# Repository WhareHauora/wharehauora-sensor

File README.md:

# whareora-sensor

# Dependencies

Tested on arduino 1.6.12

## Installing arduino

```
wget http://downloads.arduino.cc/arduino-1.6.12-linux64.tar.xz
tar xf arduino-1.6.12-linux64.tar.xz
sudo mv arduino-1.6.12 /usr/local/share/arduino
sudo ln -s /usr/local/share/arduino/arduino /usr/local/bin/arduino
```

## Programming a sensor

We are working with a fork of the
[sensebender|https://www.openhardware.io/view/1/Sensebender-Micro]
micro circuit. A (only slightly modified) copy of their
example arduino sketch is in `sense_bender` folder. Boards
purchased from sensebender (and assembled) then programmed
with this sketch will talk happily to the Whare Hauora cloud.

See also:
[Sensor Bender Board gitub](https://github.com/mysensors/SensebenderMicro)

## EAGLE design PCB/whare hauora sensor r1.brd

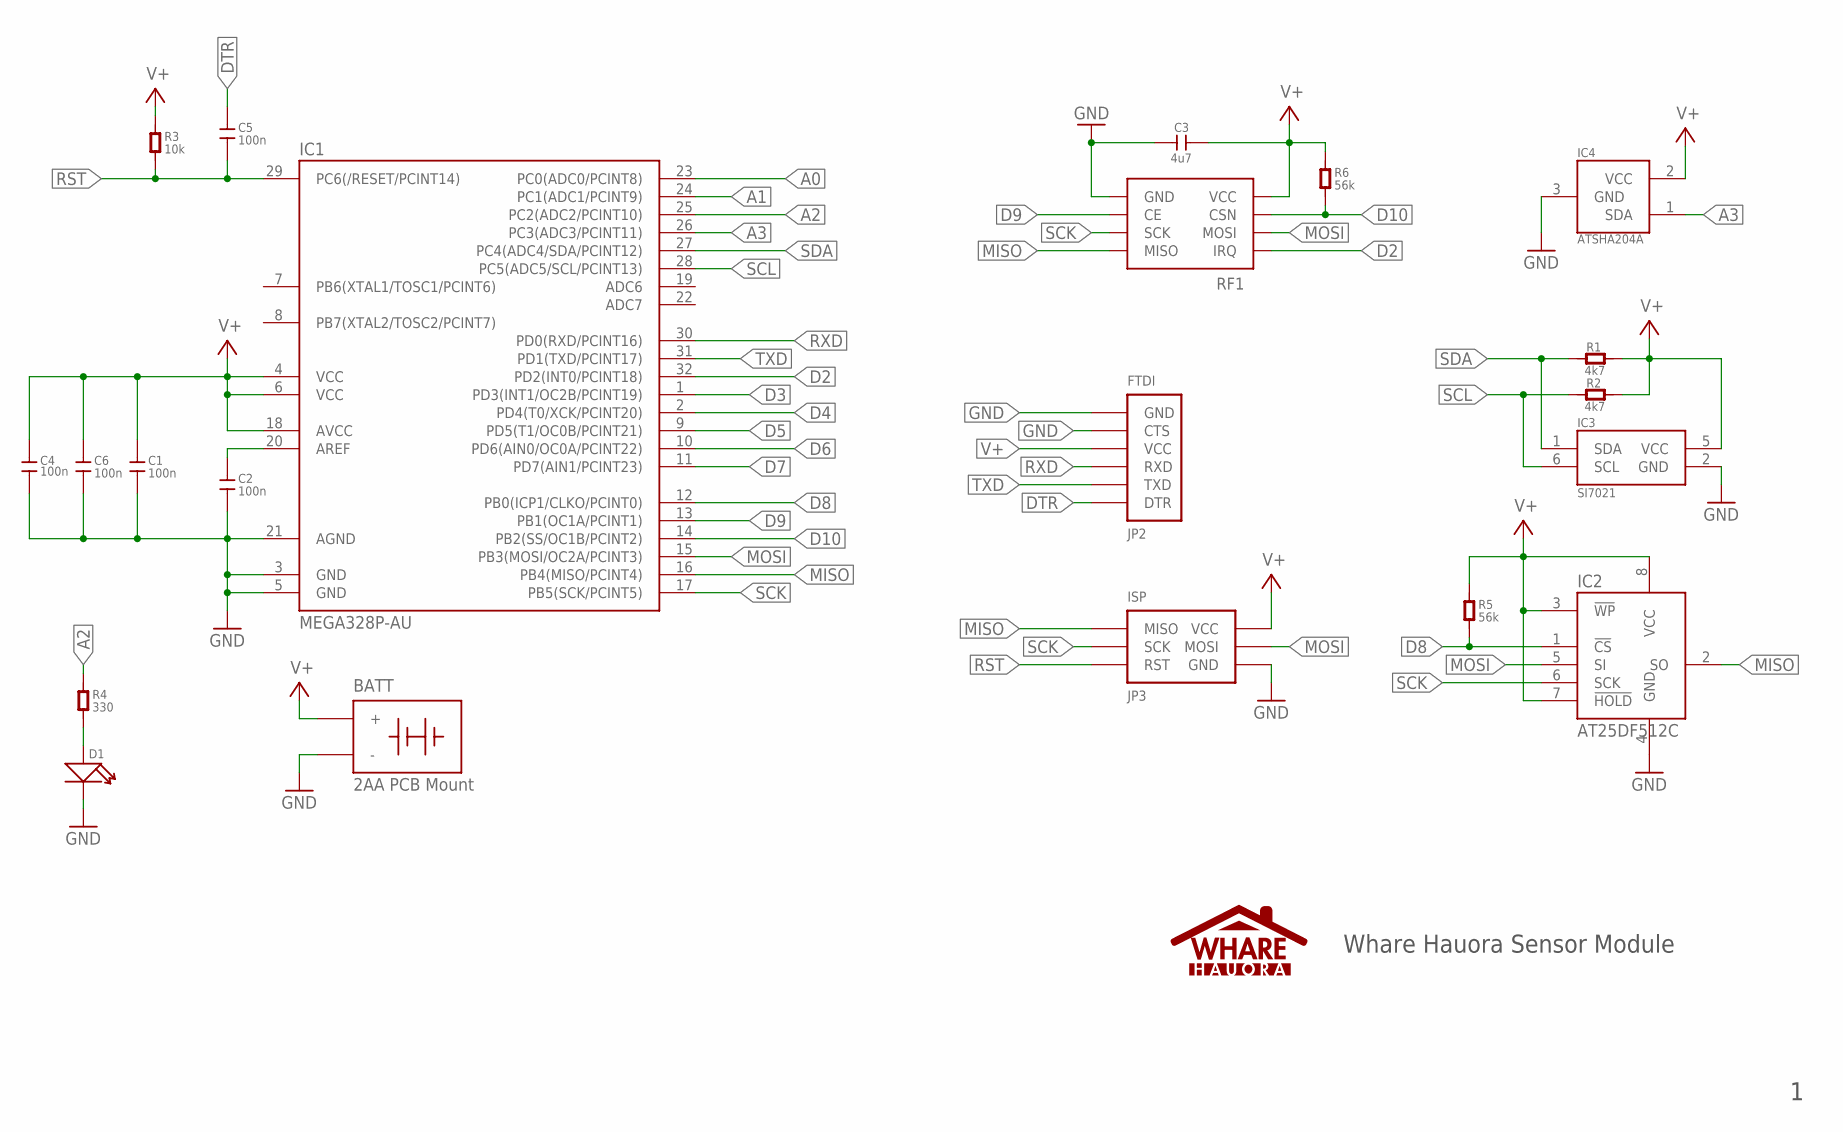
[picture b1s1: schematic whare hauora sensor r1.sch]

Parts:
BATT: 2AA-PACK; 2AA-PACK\
C1, C2, C4, C5, C6: 100n; C0603
C3: 4u7; C0603
D1: LED-0603
IC1: MEGA328P-AU; TQFP32-08
IC2: AT25DF512C; SO8
IC3: SI7021; DFN6
IC4: ATSHA204A; SOT23
JP2: FTDI
JP3: ISP
R1, R2: 4k7; R0603
R3: 10k; R0603
R4: 330; R0603
R5, R6: 56k; R0603
RF1: NRF24L01+

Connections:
A0: IC1.23 (PC0(ADC0/PCINT8))
A1: IC1.24 (PC1(ADC1/PCINT9))
A2: IC1.25 (PC2(ADC2/PCINT10)), R4.1
A3: IC1.26 (PC3(ADC3/PCINT11)), IC4.1 (SDA)
D2: IC1.32 (PD2(INT0/PCINT18)), RF1.P$8 (IRQ)
D3: IC1.1 (PD3(INT1/OC2B/PCINT19))
D4: IC1.2 (PD4(T0/XCK/PCINT20))
D5: IC1.9 (PD5(T1/OC0B/PCINT21))
D6: IC1.10 (PD6(AIN0/OC0A/PCINT22))
D7: IC1.11 (PD7(AIN1/PCINT23))
D8: IC1.12 (PB0(ICP1/CLKO/PCINT0)), IC2.1 (!CS), R5.1
D9: IC1.13 (PB1(OC1A/PCINT1)), RF1.P$3 (CE)
D10: IC1.14 (PB2(SS/OC1B/PCINT2)), R6.1, RF1.P$4 (CSN)
DTR: C5.1, JP2.DTR
GND: BATT.-, C1.2, C2.2, C3.1, C4.2, C6.2, D1.-, IC1.3 (GND), IC1.5 (GND), IC1.21 (AGND), IC2.4 (GND), IC3.2 (GND), IC4.3 (GND), JP2.CTS, JP2.GND, JP3.GND, RF1.P$1 (GND)
MISO: IC1.16 (PB4(MISO/PCINT4)), IC2.2 (SO), JP3.MISO, RF1.P$7 (MISO)
MOSI: IC1.15 (PB3(MOSI/OC2A/PCINT3)), IC2.5 (SI), JP3.MOSI, RF1.P$6 (MOSI)
unnamed: D1.+, R4.2
unnamed: C2.1, IC1.20 (AREF)
RST: C5.2, IC1.29 (PC6(/RESET/PCINT14)), JP3.RST, R3.1
RXD: IC1.30 (PD0(RXD/PCINT16)), JP2.RXD
SCK: IC1.17 (PB5(SCK/PCINT5)), IC2.6 (SCK), JP3.SCK, RF1.P$5 (SCK)
SCL: IC1.28 (PC5(ADC5/SCL/PCINT13)), IC3.6 (SCL), R2.1
SDA: IC1.27 (PC4(ADC4/SDA/PCINT12)), IC3.1 (SDA), R1.1
TXD: IC1.31 (PD1(TXD/PCINT17)), JP2.TXD
V+: BATT.+, C1.1, C3.2, C4.1, C6.1, IC1.4 (VCC), IC1.6 (VCC), IC1.18 (AVCC), IC2.3 (!WP), IC2.7 (!HOLD), IC2.8 (VCC), IC3.5 (VCC), IC4.2 (VCC), JP2.VCC, JP3.VCC, R1.2, R2.2, R3.2, R5.2, R6.2, RF1.P$2 (VCC)

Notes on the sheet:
Whare Hauora Sensor Module

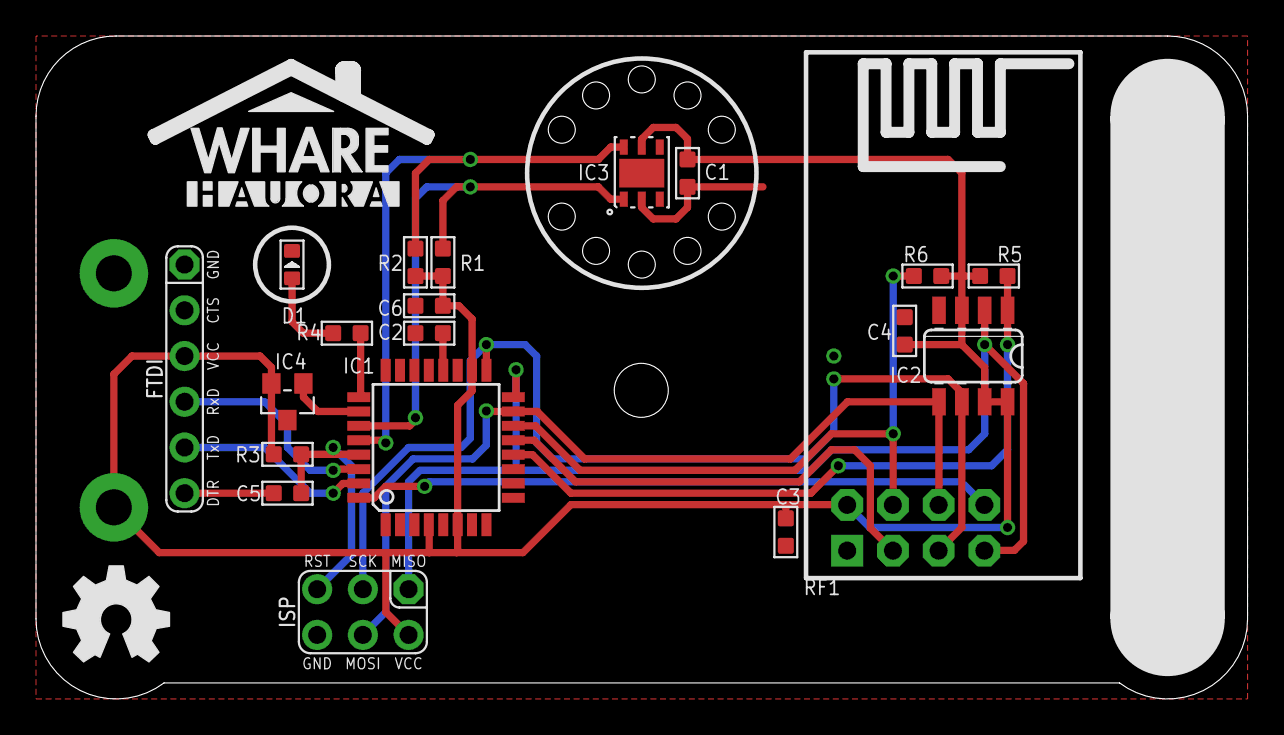
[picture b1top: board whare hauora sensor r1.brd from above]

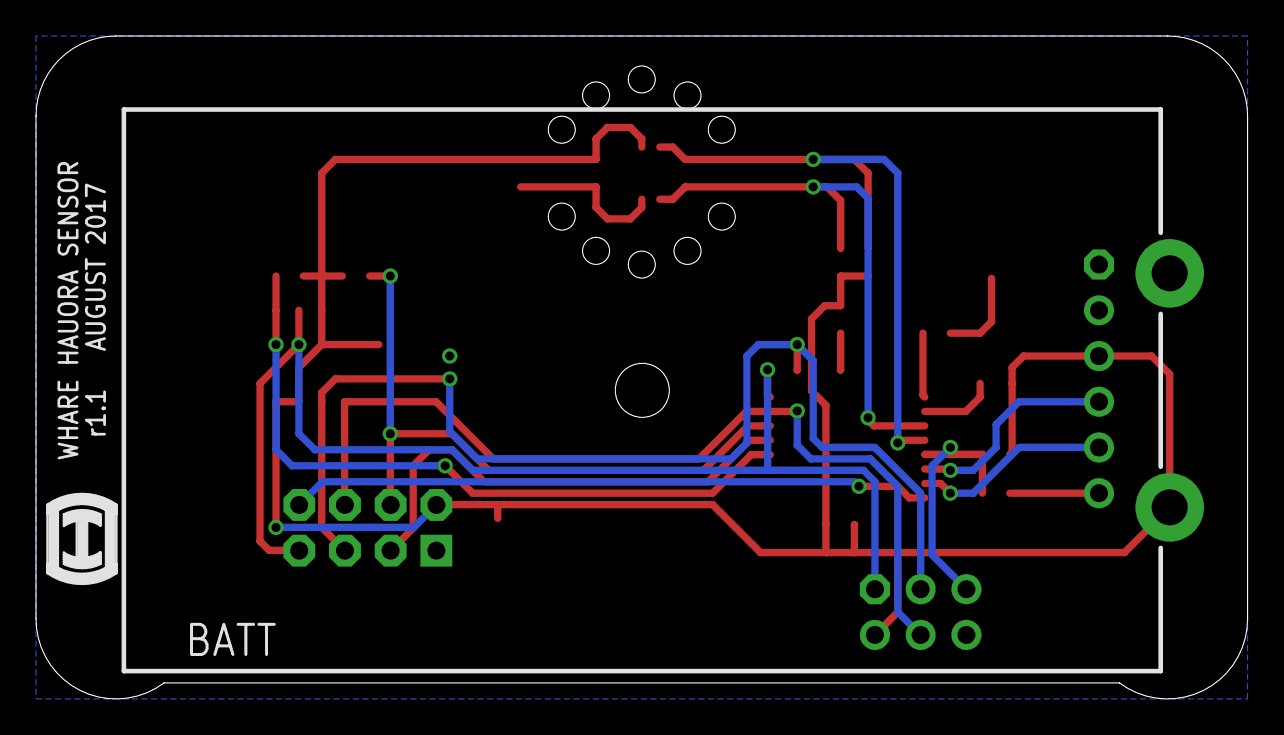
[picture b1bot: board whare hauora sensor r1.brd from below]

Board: 2 copper layers, 67.3 x 36.8 mm, 24 parts (2 on the bottom side), 19 nets.

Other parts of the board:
U$1: OSHW-LOGO
U$2: WHAREHAUORA-SMALL
U$4: MY-LOGO-SMALL

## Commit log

2016-06-02 arduino so far
2016-06-03 copied licence to one file
2016-06-03 Readme
2016-06-03 moved gateway to it's own repo
2016-07-15 upgrade to mysensors 2.0.0
2016-09-27 Down to one file
2016-09-27 removed old version of code
2016-09-27 removed repeater
2016-09-27 adding Travis file, for CI
2016-09-27 Adding library versions to the travis install
2016-09-27 build status badge
2016-09-27 Moved dependencies installation to a script
2016-09-27 Readme update
2016-12-12 Turn off verbose logging
2016-12-12 Switch to adafruit unified sensors DHT
2016-12-12 Declare our two messages earlier
2016-12-12 Present as WhareSensor 2.1
2016-12-12 hashbang added to install_deps.sh
2016-12-12 Install all dependencies from tar ball
2016-12-12 Echo what we are doing install.sh
2016-12-12 Moved install of arduino ide to install.sh
2016-12-12 Overcommit says no trailing spaces
2016-12-12 Run overcommit from travis
2016-12-12 Sign overcommit on travis
2016-12-12 Hard tabs checked by overcommit
2016-12-12 Removed overcommit from travis
    it needs a newer ruby
2016-12-13 Update .travis.yml
    Require sudo in travis
2016-12-13 add waffle.io badge
2016-12-13 Update .travis.yml
    set up env to make arduino ide happy to run
2016-12-13 Update .travis.yml
    fixed typo in travis.yml
2016-12-13 Moved badges together
2017-03-09 Set time between readings to 30 seconds
2017-07-21 Original Sensebender PCB Files
2017-07-23 Adding sense bender example arduino sketch
2017-07-23 Test sense bender on travis
2017-07-24 Moved files to folder
2017-07-24 New Sensor PCB Design
2017-07-24 Move arduino sketches to own folder
2017-07-24 Add linter to travis run
2017-07-24 Exclude .sch and .brd files from TrailingWhiteSpace checks
2017-07-24 New line at end of travis config file
2017-07-24 Install overcommit on travis
2017-07-24 Turn off author checking because doesn't work on travis
2017-07-31 1st Rev PCB Design
2017-08-06 PCB Update to 1.1
    Reduced overall sivze of PCB
2017-08-06 Moved original files to new folder
2017-08-06 Minor Track Change
    Fix spacing of tracks under CPU
2017-08-06 Removed gerber zip
2017-08-07 Minor Cosmetic Tweaks
2017-08-07 PCB Gerbers for construction
2017-08-13 Fixed all sensors having same node_id
2017-08-29 Minor Update
    Moved batt holder for better balance & ISP header. Updated some overlays & footprints
2017-09-08 Remove old jpeg
2017-09-08 Remove thumb.db - shouldn't be here
